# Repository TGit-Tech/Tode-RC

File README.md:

-----------------------------------------------------------------------------------
# Tode-RC
-----------------------------------------------------------------------------------
A User-Interfaced Arduino Mega Pro with Ebyte LoRa Radio.\
It's like a RF-Node but call it a 'Tode'.

- Arduino Mini Mega 2560 compatible Micro-Controller
- 1.8" TFT Display and 6-Button Keypad
- User friendly On-Controller IO configuration

See the docs/ Users-Guide for device support list and usage details including MQTT OpenHab connection abilities.

Benefits of the Tode over ESP32 LoRa Modules
- Big enough to be practical.  Small enough to be handy.
- 5V TTL-IO (Ebyte-RF 5V match, 200mW/IO power, Ready-fit for 5V Sensors)
- 54-IO pins (leaving (46) with display, keypad, radio connected)
- 30dbm (T30D) Transmission Power with Ebyte LoRa Modules (A good 5-mile distance)
- 3-Piece plug-together assembly keeps individual parts easy to swap/salvage.

Due to button sticking issues the buttons are now just black tops shown in first image.

-----------------------------------------------------------------------------------
#Project Purchase Options
-----------------------------------------------------------------------------------
Purchase pre-made at...
- https://www.tindie.com/stores/tgittech/
- https://www.etsy.com/shop/TGitTech

-----------------------------------------------------------------------------------
#Project Firmware & Expansions
-----------------------------------------------------------------------------------
- Firmware at https://github.com/TGit-Tech/Tode-RC-Firmware
	- Be sure to set Backplane model in config.h
- Side-IO Screw Terminals #SIOST (pictured) https://github.com/TGit-Tech/Tode-IO
- Back-IO Pin Header Array #BIOPH https://github.com/TGit-Tech/Tode-IO

-----------------------------------------------------------------------------------
#Project Status
-----------------------------------------------------------------------------------
USE Tode-RC.BD241S.  It supports 1W(T30D) or 1/4W(T20D) Ebyte Radios.\
Double Check that the PCB doesn't have the below design error.

Model SD23CF(In-Design/BETA) supports 2W(T33D) Radios but only 7-IO pins.
	
- Previous Release Notes
NEW changes.  The old model SA212K with analog keypad will become obsolete (not supported).
All future designs will have digital keypads as analog was spotty with moisture and 
temperature change.  Secondary Power Supplies are On-PCB now for both SD23CF(Side-IO) 
and BD241S(Back-IO).  Firmware will auto-detect E32-433T20D/T30D, E22-400T30D/900T30D 
and E220-400T30D Ebyte Radios.

---

# 🌐 **Tode Ecosystem**

The Tode Ecosystem offers a robust, flexible, and secure solution for managing devices in an environment where **infrastructure is not required**. It’s designed to seamlessly integrate with the **RF-DITS** protocol, providing a communication framework for device control, alarm propagation, and security.

## 🚀 **Overview**

The Tode Ecosystem empowers devices to function autonomously or in **P2P** (peer-to-peer) networks, providing an **infrastructure-free solution** for industrial, home, and remote applications. With its **5V EMT-resistant hardware** and powerful **virtual device** logic for alarm processing, it brings resilience and versatility to the edge of your network.

---

## 🛠️ **Key Features**

* **Non-Infrastructure Communication**: Operates **without** requiring an internet connection, server, or cloud dependencies. Devices communicate **peer-to-peer** between nodes, allowing for seamless data exchange and control.

* **RF-DITS Protocol**: The core communication protocol used by the Tode ecosystem. This protocol allows secure, fast, and efficient communication between Master and Remote nodes using **Device Index Tables (DIT)** with integrated security.

* **5V EMT Resistance**: Built to handle harsh environments, the Tode ecosystem is engineered to withstand **electromagnetic interference (EMI)**, providing reliable operation in industrial settings.

* **Virtual Device Logic**: The **Virtual Device Logic** allows users to implement custom control logic directly on the device, enabling real-time alarm processing, device manipulation, and other control functions.

* **Quick Firmware Updates**: The firmware can be quickly updated by plugging the Tode node into a wiring interface, making updates straightforward without requiring specialized equipment.

---

## 🔒 **Security**

* **SecNet (Security Network)**: The Tode ecosystem utilizes **SecNet**, a user-set security code embedded in each packet. This ensures data integrity and security. The **SecNet** code is also used as part of a challenge-response mechanism during **SETVAL** operations, preventing replay attacks and ensuring secure value updates.

* **Packet Integrity**: Every packet transmitted in the Tode network is verified for authenticity with the **SecNet** code. Only authorized devices can send or receive data securely. **SETVAL** operations are particularly secured to ensure legitimate communication.

* **Alarm Security**: Alarm messages are pushed to the designated **Remote nodes** when a condition is triggered. The **SecNet** code ensures that only authorized recipients receive the alarm notifications.

---

## ⚡ **Quick Setup & Control**

* **Device Setup**: The Tode ecosystem doesn’t require centralized infrastructure or cloud servers. Each **Master node** stores the configuration of its attached devices and is capable of sharing this configuration with **Remote nodes** using the **RF-DITS protocol**. **Remote nodes** can pull configurations and control devices according to those settings.

* **Time-Sensitive Updates**: Alarm conditions are pushed immediately to all **Remote nodes** without unnecessary overhead. Value updates can be requested by the remote node through the **RF-DITS protocol**, ensuring efficient communication.

---

## 📈 **Key Advantages Over Common IoT Platforms**

| **Key Advantage**             | **Tode Ecosystem (RF-DITS)**                                                                           | **Common IoT Platforms**                                                        |
| ----------------------------- | ------------------------------------------------------------------------------------------------------ | ------------------------------------------------------------------------------- |
| **Infrastructure**            | Operates **without** internet or server dependencies, functioning in **peer-to-peer** mode.            | Requires cloud, servers, or centralized hubs for device control                 |
| **Portability**               | **Portable** control with remote nodes in P2P communication.                                           | Typically dependent on fixed infrastructure                                     |
| **Data Integrity**            | Secured communication with **SecNet** protecting packets and ensuring valid data exchange.             | Often lacks robust security or packet verification                              |
| **Low Airtime Communication** | Optimized communication with **DIT** table, reducing airtime usage for value exchanges.                | Typically uses more airtime due to polling systems and continuous communication |
| **Alarm Handling**            | **One-time push** of alarms to Remote nodes, minimizing network traffic.                               | Continuous polling for alarm conditions, leading to higher network usage        |
| **Device Control**            | Full **control** over devices with direct value setting, updating, and logic processing.               | Remote devices may be read but not easily controlled depending on the platform  |
| **EMT Resistance**            | Designed to handle **electromagnetic interference (EMI)** in industrial environments.                  | Sensitive to environmental EMI interference, which can disrupt performance      |
| **Firmware Updates**          | **Easy and fast** firmware updates via a wiring interface—no internet or specialized equipment needed. | Over-the-air updates typically require internet access and cloud dependencies   |
| **Flexible Control Logic**    | **Virtual device logic** allows for custom control and alarm processing locally on the device.         | Often lacks flexibility for local control and relies on cloud logic             |

---

## ⚙️ **Protocol Breakdown: RF-DITS**

### **Device Index Table with Security (DITS)**

Each node maintains a **Device Index Table (DIT)** that lists the connected devices by index. This table helps the **Master node** store and transmit configurations for each attached device to **Remote nodes**.

* **Master Node**: Stores and manages the configuration of devices, pushes alarm notifications, and shares device settings with **Remote nodes**.
* **Remote Node**: Pulls device configurations from the **Master node** and can manipulate values according to the stored configuration.

### **Alarms**

* **Alarm Handling**: When an alarm condition is triggered on the **Master node**, an alarm packet is sent to all **Remote nodes** on the recipient list.
* **No Acknowledgment Required**: The alarm is a **one-time push** with no response required from the **Remote nodes**.
* **Alarm Recipient List**: The **Master node** stores a list of **Remote node** addresses, which is dynamically updated with each communication, including value requests. Manual pruning of the list is also possible.

---

## 🔗 **Integration with External Systems**

While the Tode ecosystem operates **without the need for internet infrastructure**, it can optionally integrate with systems such as **MQTT**, **OpenHAB**, or **Home Assistant** through an MQTT bridge.

This optional feature allows:

* **Pulling Device Values**: Remote nodes can request device values from **Master nodes** on a regular schedule or based on events.
* **Pushing Alarms**: When an alarm condition is triggered, the **Master node** can push the alarm data to an MQTT broker, which allows external systems to act on the alarm.

However, it's important to note that **Tode's core functionality** works without cloud connectivity, and the MQTT integration is entirely optional.

---

## 🔑 **Hardware Advantages**

Tode nodes are designed to operate in **industrial environments** where **electromagnetic interference (EMI)** is common, and devices need to withstand harsh conditions. The **5V EMT-resistant hardware** ensures the Tode ecosystem works reliably even in settings that may disrupt other IoT systems.

---

## 🛠️ **Getting Started**

1. **Set Up the Master Node**: Connect and configure devices on the **Master node**. Store configurations and define which devices you want to control.
2. **Add Remote Nodes**: Manually enter the **Master node's** address into the **Remote nodes** to establish communication and pull device configurations.
3. **Manage Alarms and Control**: Configure alarm conditions on the **Master node**. Alarms will be **pushed** to all **Remote nodes**.
4. **Firmware Updates**: Simply plug the Tode node into the wiring interface to update its firmware without requiring internet access.

---

## 📚 **Conclusion**

The **Tode Ecosystem** offers a resilient, flexible, and secure solution for edge-device control in environments where **infrastructure** is not an option. Its core **RF-DITS protocol** and **5V EMT resistance** provide reliable communication, while its optional integration with systems like **MQTT** makes it versatile for a range of applications.

---

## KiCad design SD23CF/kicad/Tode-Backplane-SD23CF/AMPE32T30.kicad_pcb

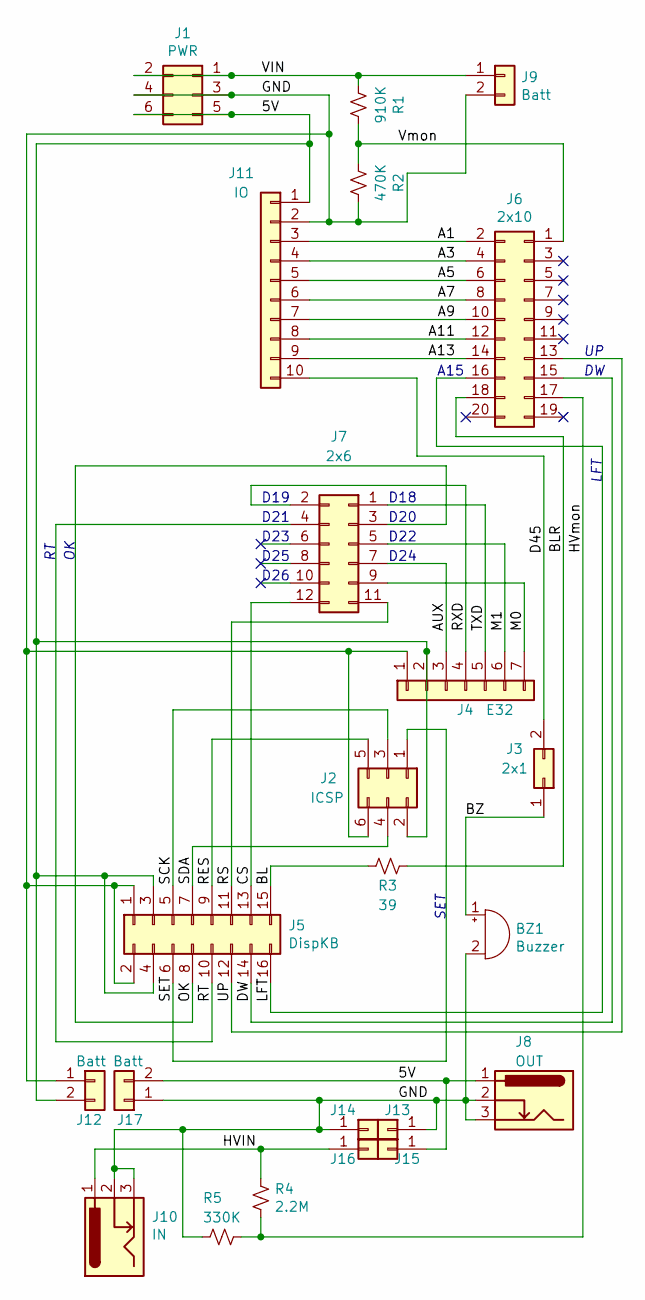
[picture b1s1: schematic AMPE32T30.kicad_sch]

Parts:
BZ1: Buzzer; MagneticBuzzer_PUI_AT-0927-TT-6-R
J1: PWR; PinSocket_2x03_P2.54mm_Vertical
J2: ICSP; PinHeader_2x03_P2.54mm_Vertical
J3: 2x1; PinSocket_1x02_P2.54mm_Vertical
J4: E32; PinSocket_1x07_P2.54mm_Vertical
J5: DispKB; PinSocket_2x08_P2.54mm_Vertical
J6: 2x10; PinSocket_2x10_P2.54mm_Vertical
J7: 2x6; PinSocket_2x06_P2.54mm_Vertical
J8: OUT; BarrelJack_Horizontal
J9, J12, J17: Batt; SolderWire-0.5sqmm_1x02_P4.6mm_D0.9mm_OD2.1mm
J10: IN; BarrelJack_Horizontal
J11: IO; PinSocket_1x10_P2.54mm_Vertical
J13: 13; PinSocket_1x01_P2.54mm_Vertical
J14: 14; PinSocket_1x01_P2.54mm_Vertical
J15: 15; PinSocket_1x01_P2.54mm_Vertical
J16: 16; PinSocket_1x01_P2.54mm_Vertical
R1: 910K; R_0805_2012Metric_Pad1.20x1.40mm_HandSolder
R2: 470K; R_0805_2012Metric_Pad1.20x1.40mm_HandSolder
R3: 39; R_0805_2012Metric_Pad1.20x1.40mm_HandSolder
R4: 2.2M; R_0805_2012Metric_Pad1.20x1.40mm_HandSolder
R5: 330K; R_0805_2012Metric_Pad1.20x1.40mm_HandSolder

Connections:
/5V: J1.5, J1.6, J2.2, J4.2, J5.3, J5.4, J8.1, J11.1, J12.2, J15.1, J17.2
/A1: J6.2, J11.3
/A3: J6.4, J11.4
/A5: J6.6, J11.5
/A7: J6.8, J11.6
/A9: J6.10, J11.7
/A11: J6.12, J11.8
/A13: J6.14, J11.9
/AUX: J4.3, J7.7
/BL: J5.15, R3.2
/BLR: J6.18, R3.1
/BZ: BZ1.1 (-), J3.1
/CS: J5.13, J7.12
/D45: J3.2, J11.10
/DW: J5.14, J6.15
/GND: BZ1.2 (+), J1.3, J1.4, J2.6, J4.1, J5.1, J5.2, J8.2, J8.3, J9.2, J10.2, J10.3, J11.2, J12.1, J13.1, J14.1, J17.1, R2.1, R5.2
/HVIN: J10.1, J16.1, R4.2
/HVmon: J6.17, R4.1, R5.1
/LFT: J5.16, J6.16
/M0: J4.7, J7.9
/M1: J4.6, J7.5
/OK: J5.8, J7.3
/RES: J2.5, J5.9
/RS: J5.11, J7.11
/RT: J5.10, J7.4
/RXD: J4.4, J7.2
/SCK: J2.3, J5.5
/SDA: J2.4, J5.7
/SET: J2.1, J5.6
/TXD: J4.5, J7.1
/UP: J5.12, J6.13
/VIN: J1.1, J1.2, J9.1, R1.2
/Vmon: J6.1, R1.1, R2.2

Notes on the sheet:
LFT
D18
D25
SET
D23
D24
D20
D26
D19
A15
D22
D21

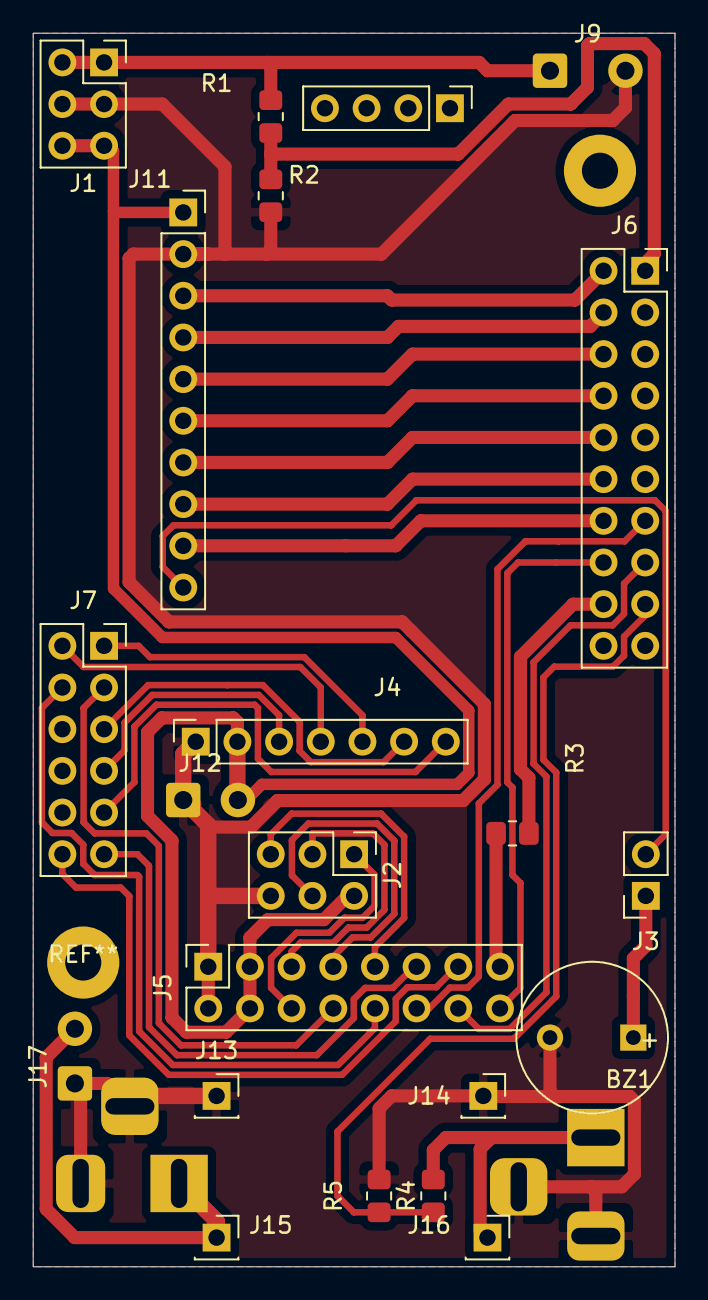
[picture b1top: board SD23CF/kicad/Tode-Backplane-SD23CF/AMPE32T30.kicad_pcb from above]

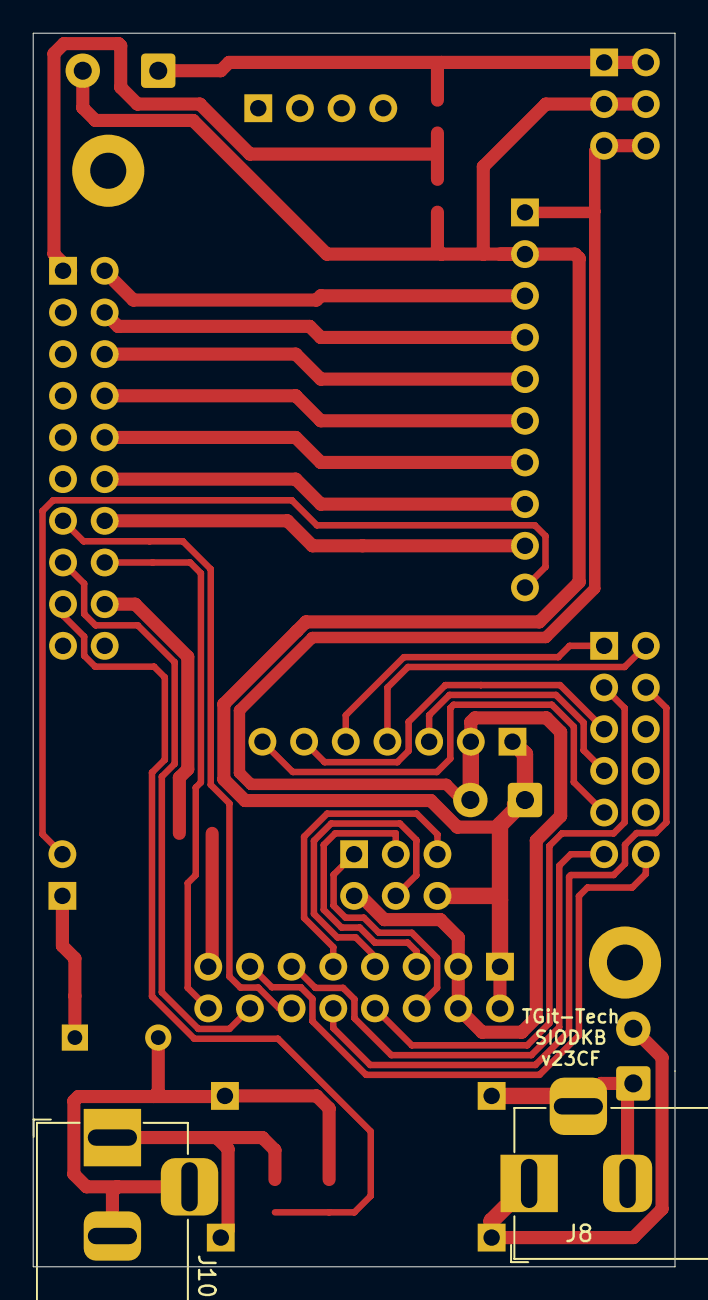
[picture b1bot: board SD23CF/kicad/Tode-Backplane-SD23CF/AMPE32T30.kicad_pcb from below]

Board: 2 copper layers, 39.1 x 75.2 mm, 23 parts (2 on the bottom side), 33 nets.

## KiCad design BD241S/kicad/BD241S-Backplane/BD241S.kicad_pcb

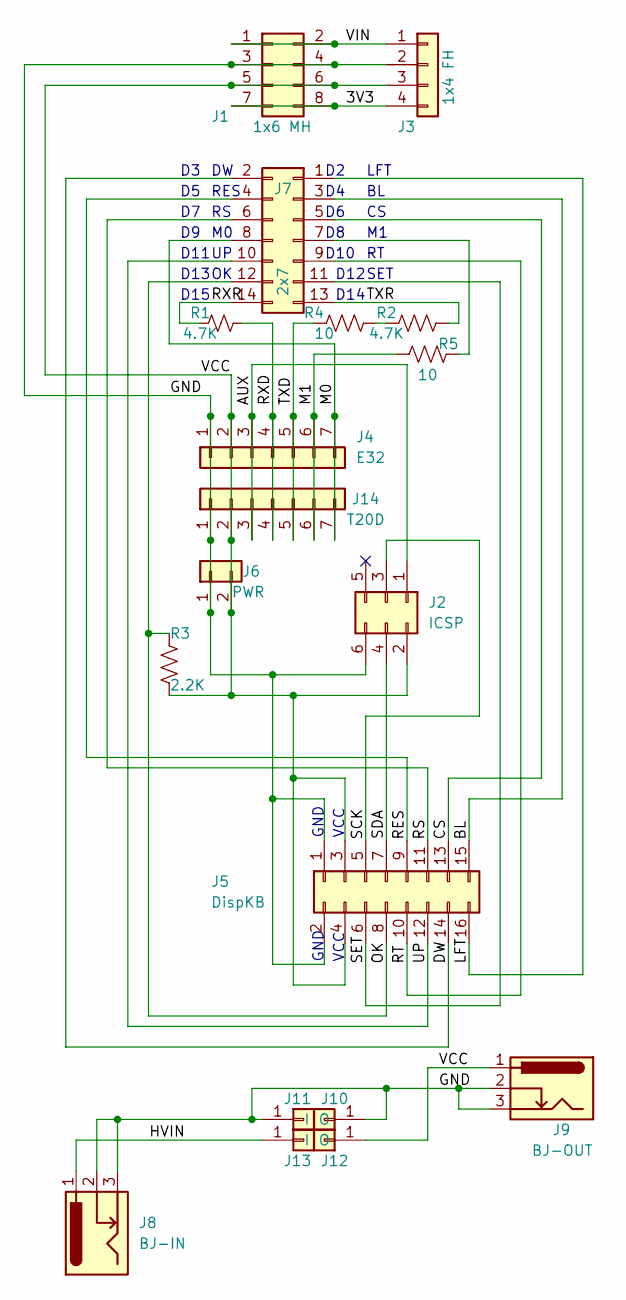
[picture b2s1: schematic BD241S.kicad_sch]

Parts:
J1: 1x6 MH; PinSocket_2x04_P2.54mm_Vertical
J2: ICSP; PinHeader_2x03_P2.54mm_Vertical
J3: 1x4 FH; PinSocket_1x04_P2.54mm_Vertical
J4: E32; PinSocket_1x07_P2.54mm_Vertical
J5: DispKB; PinSocket_2x08_P2.54mm_Vertical
J6: PWR; PinSocket_1x02_P2.54mm_Vertical
J7: 2x7; PinSocket_2x07_P2.54mm_Vertical
J8: BJ-IN; BarrelJack_Horizontal
J9: BJ-OUT; BarrelJack_Horizontal
J10, J12: O; PinSocket_1x01_P2.54mm_Vertical
J11, J13: I; PinSocket_1x01_P2.54mm_Vertical
J14: T20D; PinSocket_1x07_P2.54mm_Vertical
R1, R2: 4.7K; R_0805_2012Metric_Pad1.20x1.40mm_HandSolder
R3: 2.2K; R_0805_2012Metric_Pad1.20x1.40mm_HandSolder
R4, R5: 10; R_0805_2012Metric_Pad1.20x1.40mm_HandSolder

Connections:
/3V3: J1.7, J1.8, J3.4
/AUX: J2.1, J4.3, J14.3
/BL: J5.15, J7.3
/CS: J5.13, J7.5
/DW: J5.14, J7.2
/GND: J1.3, J1.4, J2.6, J3.2, J4.1, J5.1, J5.2, J6.1, J8.2, J8.3, J9.2, J9.3, J10.1, J11.1, J14.1
/HVIN: J8.1, J13.1
/LFT: J5.16, J7.1
/M0: J4.7, J7.8, J14.7
/M1: J4.6, J14.6, R5.1
/OK: J5.8, J7.12, R3.2
/RES: J5.9, J7.4
/RS: J5.11, J7.6
/RT: J5.10, J7.9
/RXD: J4.4, J14.4, R1.1
/RXR: J7.14, R1.2
/SCK: J2.3, J5.5
/SDA: J2.4, J5.7
/SET: J5.6, J7.11
/TXD: J4.5, J14.5, R4.1
/TXR: J7.13, R2.2
/UP: J5.12, J7.10
/VCC: J1.5, J1.6, J2.2, J3.3, J4.2, J5.3, J5.4, J6.2, J9.1, J12.1, J14.2, R3.1
/VIN: J1.1, J1.2, J3.1
unnamed: J7.7, R5.2
unnamed: R2.1, R4.2

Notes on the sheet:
GND
LFT
D13
RES
SET
D12
D15
VCC
D14
D10
D11

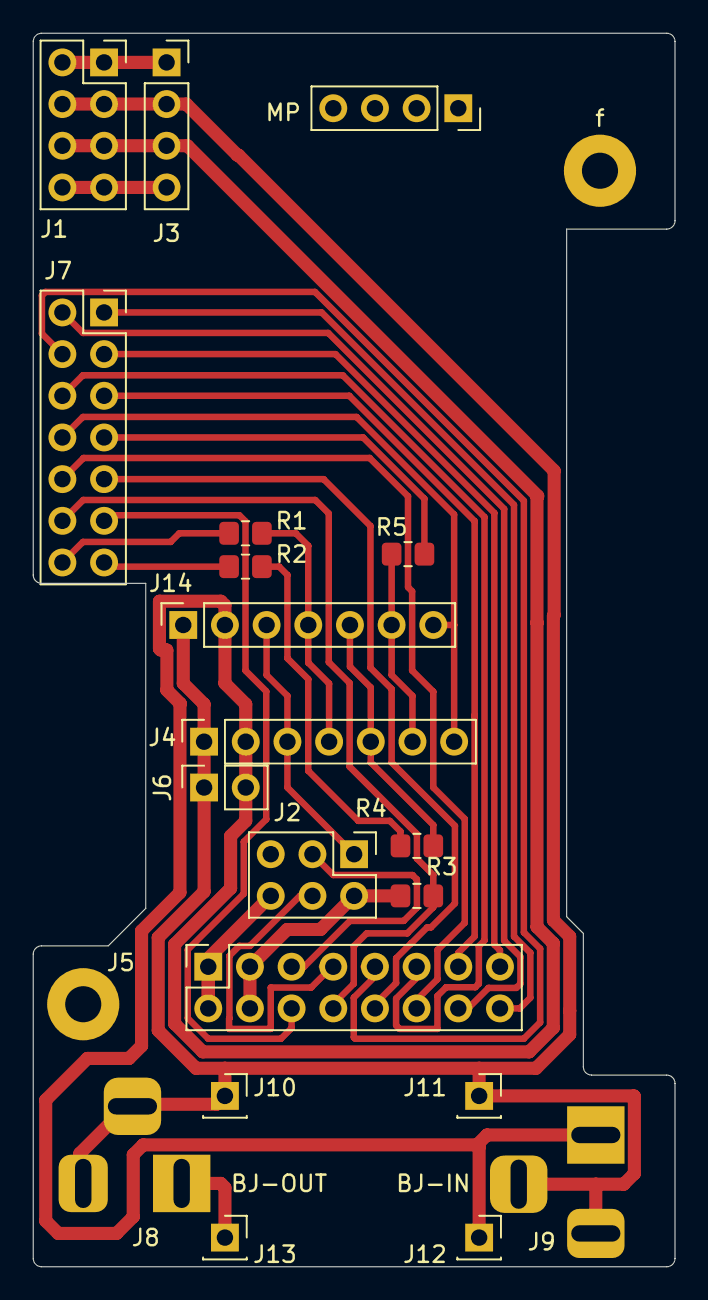
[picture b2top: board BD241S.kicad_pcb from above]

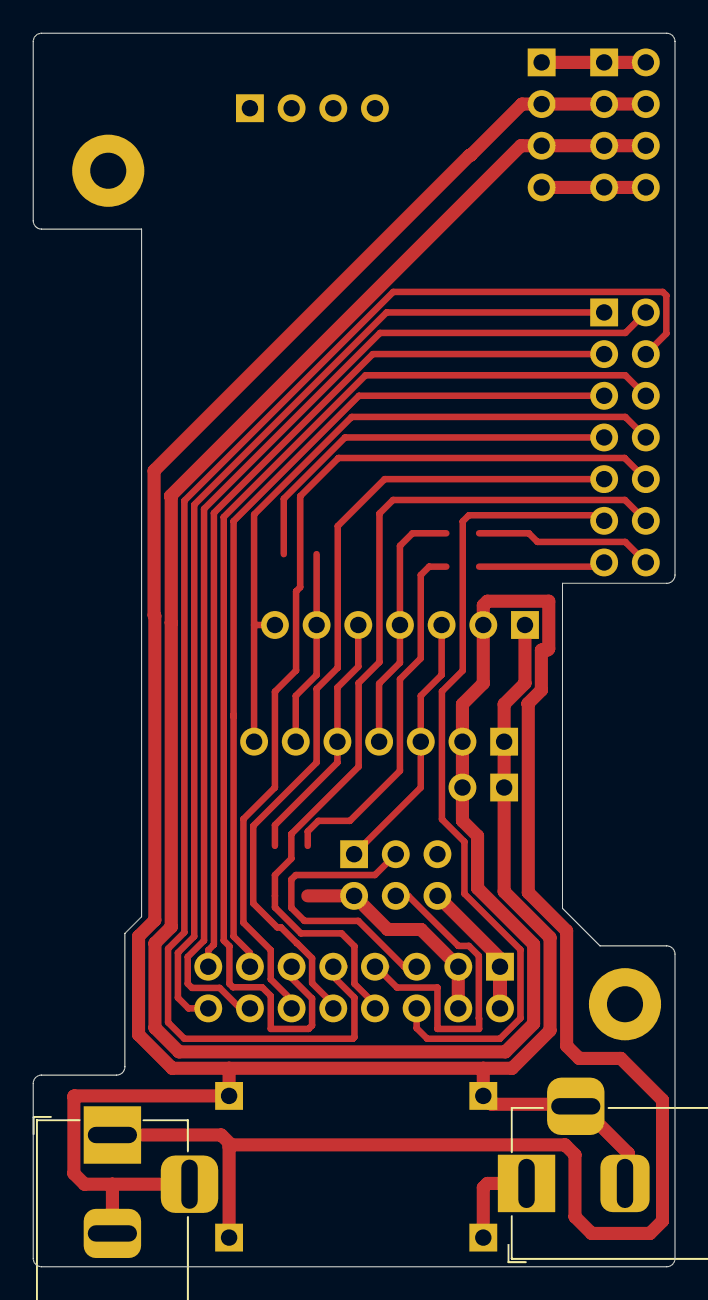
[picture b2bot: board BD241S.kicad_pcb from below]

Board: 2 copper layers, 39.1 x 75.2 mm, 22 parts (2 on the bottom side), 26 nets.

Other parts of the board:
MP: PinSocket_1x04_P2.54mm_Vertical
e: MountingHole_2.2mm_M2_Pad
f: MountingHole_2.2mm_M2_Pad

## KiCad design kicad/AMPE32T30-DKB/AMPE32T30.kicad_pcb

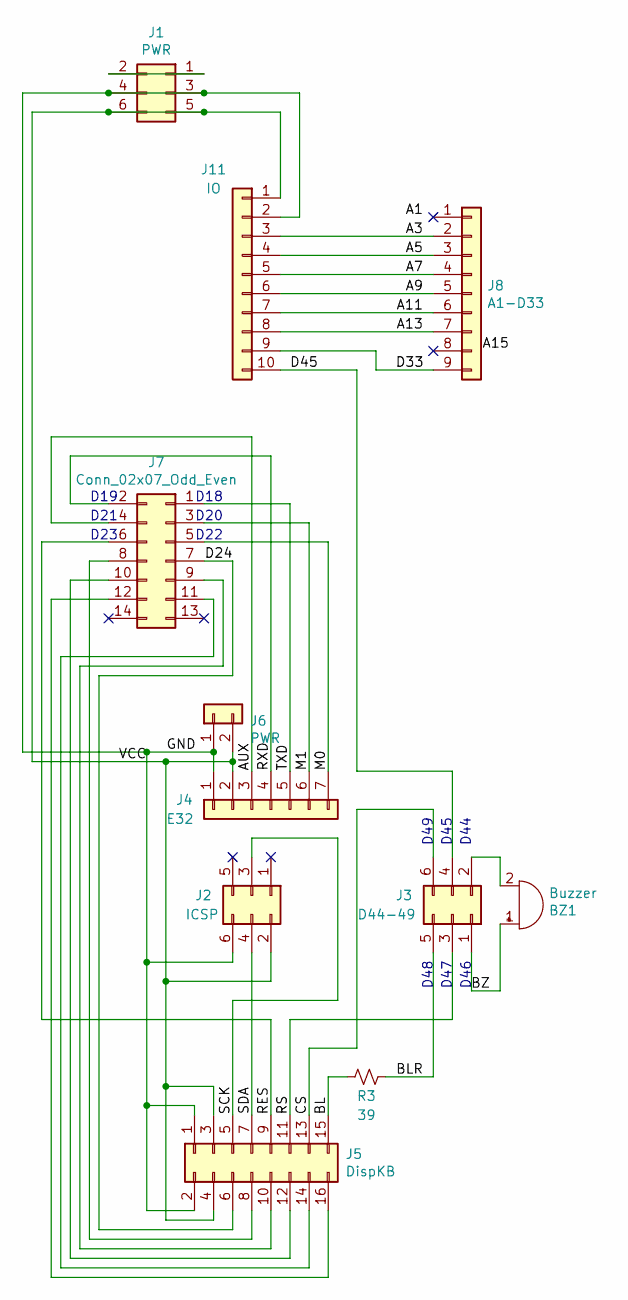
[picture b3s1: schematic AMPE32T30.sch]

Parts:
BZ1: Buzzer; MagneticBuzzer_PUI_AT-0927-TT-6-R
J1: PWR; PinSocket_2x03_P2.54mm_Vertical
J2: ICSP; PinHeader_2x03_P2.54mm_Vertical
J3: D44-49; PinSocket_2x03_P2.54mm_Vertical
J4: E32; PinSocket_1x07_P2.54mm_Vertical
J5: DispKB; PinSocket_2x08_P2.54mm_Vertical
J6: PWR; PinSocket_1x02_P2.54mm_Vertical
J7: Conn_02x07_Odd_Even; PinSocket_2x07_P2.54mm_Vertical
J8: A1-D33; PinSocket_1x09_P2.54mm_Vertical
J11: IO; PinSocket_1x10_P2.54mm_Vertical
R3: 39; R_0805_2012Metric_Pad1.20x1.40mm_HandSolder

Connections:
/A3: J8.2, J11.3
/A5: J8.3, J11.4
/A7: J8.4, J11.5
/A9: J8.5, J11.6
/A11: J8.6, J11.7
/A13: J8.7, J11.8
/AUX: J4.3, J7.4
/BL: J5.15, R3.2
/BLR: J3.5, R3.1
/BZ: BZ1.1 (-), J3.1
/CS: J3.6, J5.13
/D24: J5.6, J7.7
/D33: J8.9, J11.9
/D45: J3.4, J11.10
/GND: J1.3, J1.4, J2.6, J4.1, J5.1, J5.2, J6.1, J11.2
/M0: J4.7, J7.5
/M1: J4.6, J7.3
/RES: J5.9, J7.6
/RS: J3.3, J5.11
/RXD: J4.4, J7.2
/SCK: J2.3, J5.5
/SDA: J2.4, J5.7
/TXD: J4.5, J7.1
/VCC: J1.5, J1.6, J2.2, J4.2, J5.3, J5.4, J6.2, J11.1
unnamed: BZ1.2 (+), J3.2
unnamed: J1.1, J1.2
unnamed: J5.8, J7.8
unnamed: J5.10, J7.9
unnamed: J5.12, J7.10
unnamed: J5.14, J7.11
unnamed: J5.16, J7.12

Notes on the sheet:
D46
D47
D48
D49
D45
D44
D23
D21
D19
D18
D20
D22

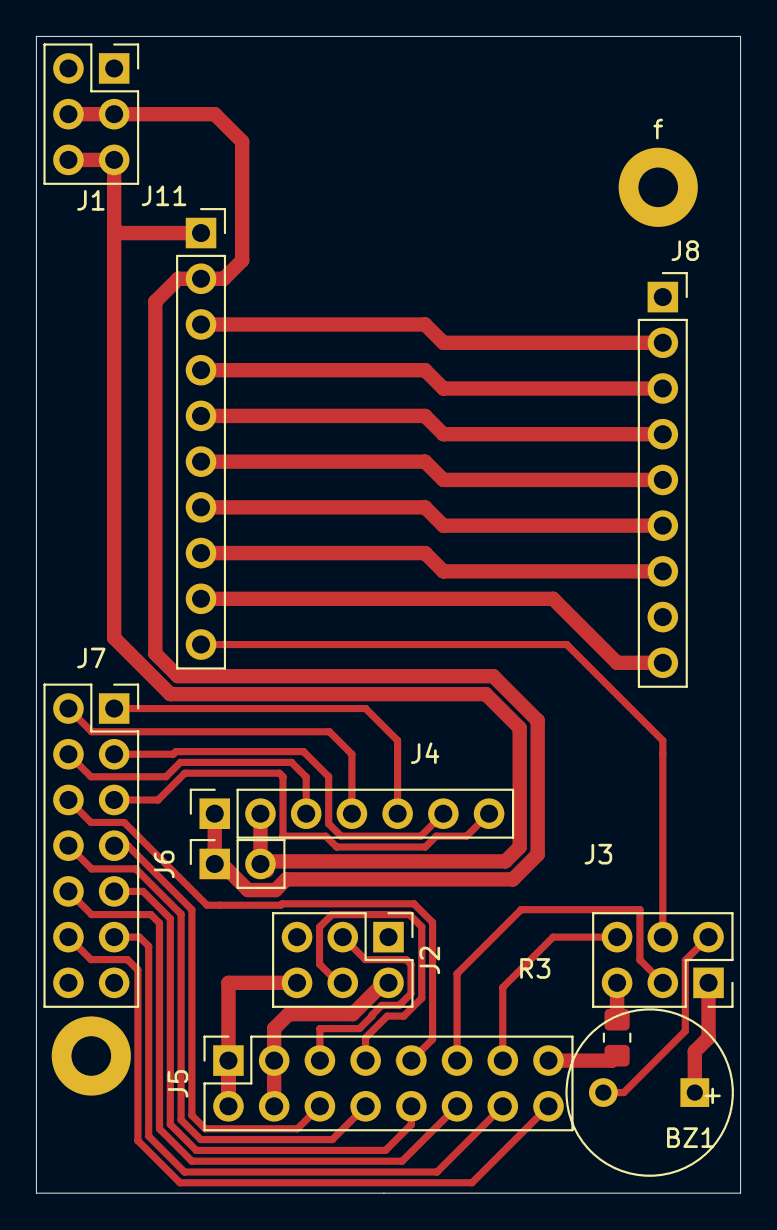
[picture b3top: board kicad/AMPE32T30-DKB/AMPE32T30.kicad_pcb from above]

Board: 2 copper layers, 39.1 x 64.3 mm, 13 parts (0 on the bottom side), 31 nets.

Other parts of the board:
e: MountingHole_2.2mm_M2_Pad
f: MountingHole_2.2mm_M2_Pad

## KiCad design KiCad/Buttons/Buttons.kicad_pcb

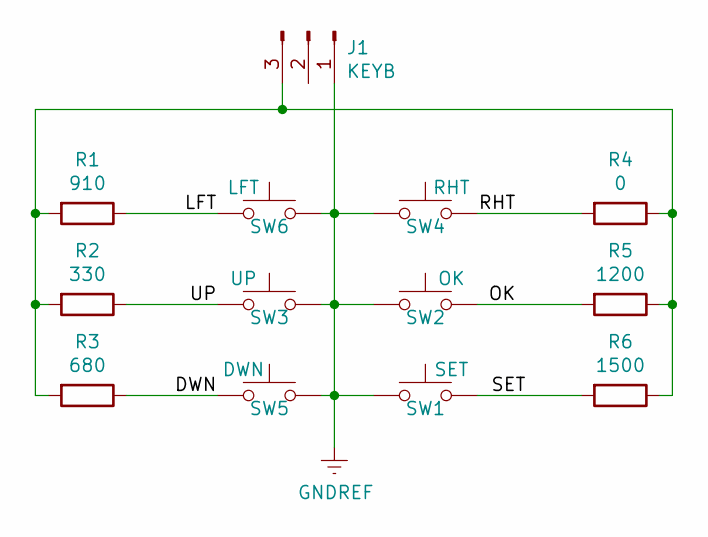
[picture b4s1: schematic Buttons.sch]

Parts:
J1: KEYB; PinHeader_1x03_P2.54mm_Vertical
R1: 910; R_0805_2012Metric
R2: 330; R_0805_2012Metric
R3: 680; R_0805_2012Metric
R4: 0; R_0805_2012Metric
R5: 1200; R_0805_2012Metric
R6: 1500; R_0805_2012Metric
SW1: SET; SW_PUSH_6mm
SW2: OK; SW_PUSH_6mm
SW3: UP; SW_PUSH_6mm
SW4: RHT; SW_PUSH_6mm
SW5: DWN; SW_PUSH_6mm
SW6: LFT; SW_PUSH_6mm

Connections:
/5V: J1.2; also elsewhere on the board
/AKB: J1.3, R1.2, R2.2, R3.2, R4.1, R5.1, R6.1
/DWN: R3.1, SW5.1
/LFT: R1.1, SW6.1
/OK: R5.2, SW2.2
/RHT: R4.2, SW4.2
/SET: R6.2, SW1.2
/UP: R2.1, SW3.1
GNDREF: J1.1, SW1.1, SW2.1, SW3.2, SW4.1, SW5.2, SW6.2; also elsewhere on the board

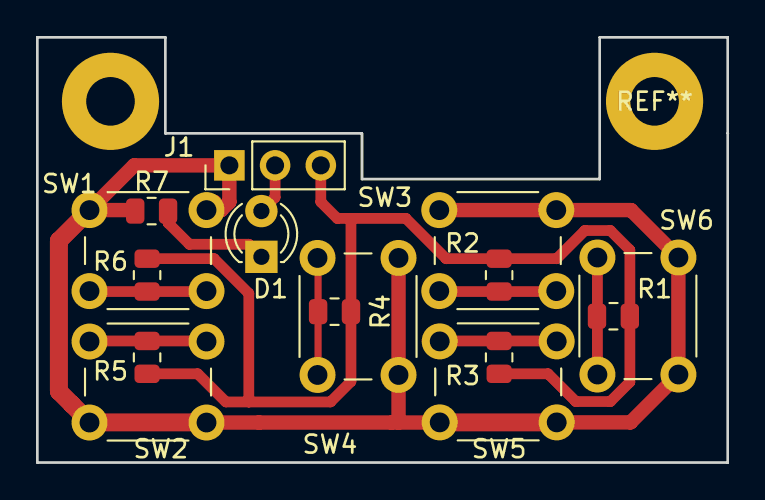
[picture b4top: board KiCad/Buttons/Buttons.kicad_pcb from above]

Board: 2 copper layers, 38.4 x 23.6 mm, 15 parts (0 on the bottom side), 10 nets.

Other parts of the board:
D1: LED; LED_D3.0mm
R7: R; R_0805_2012Metric

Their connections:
/5V: D1.2; also elsewhere on the board
GNDREF: R7.1; also elsewhere on the board
unnamed: D1.1, R7.2

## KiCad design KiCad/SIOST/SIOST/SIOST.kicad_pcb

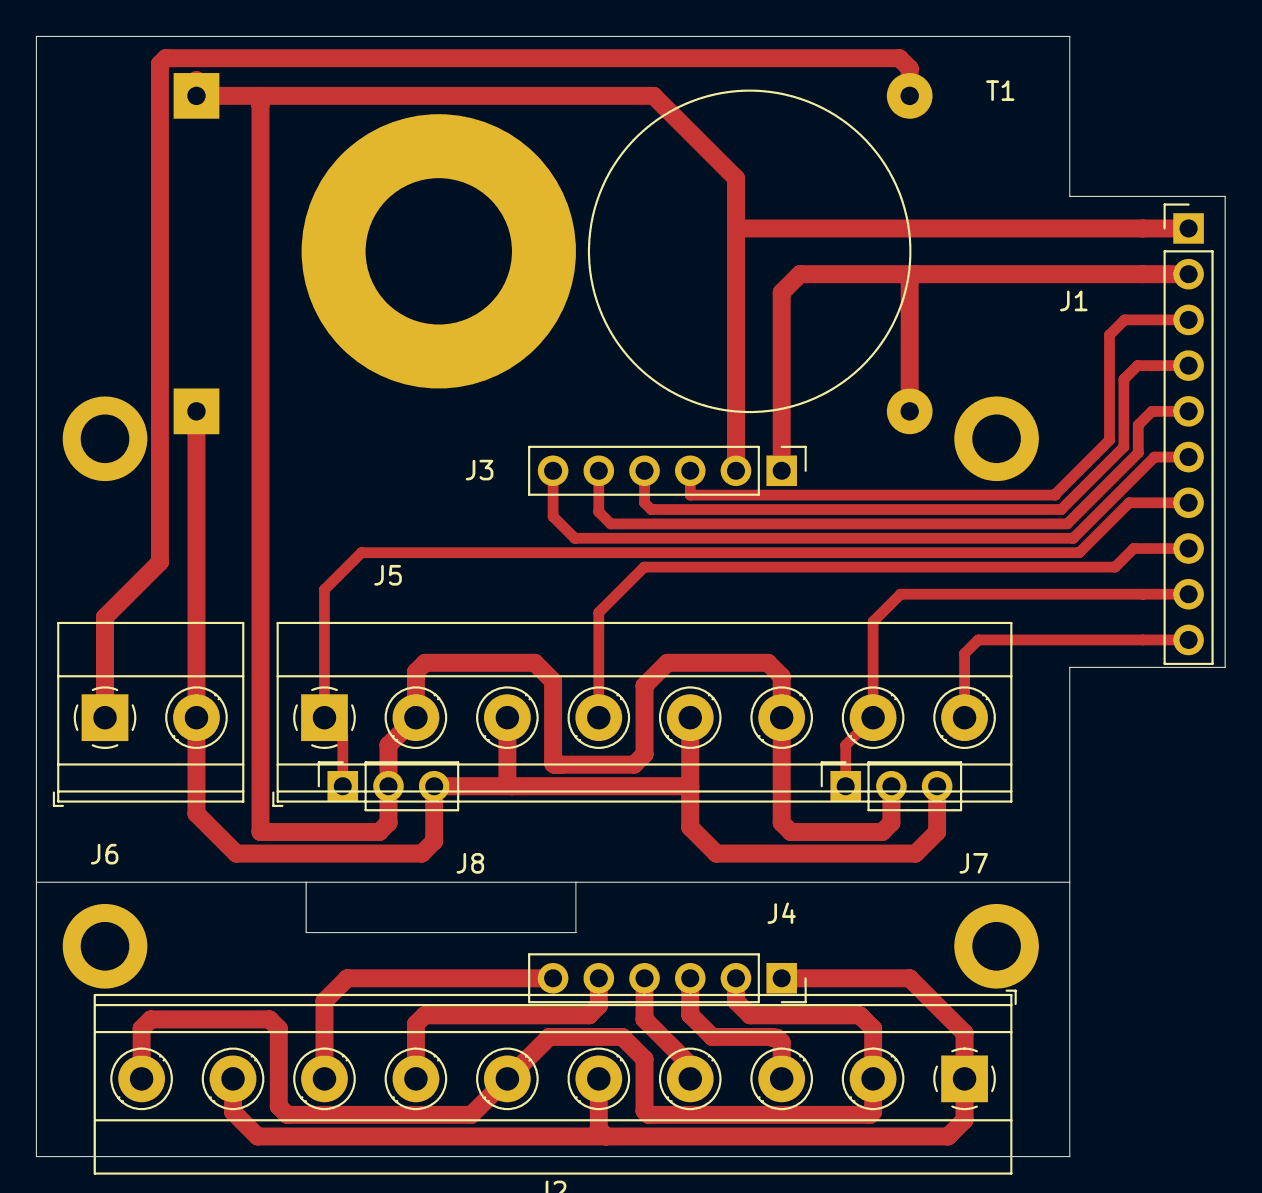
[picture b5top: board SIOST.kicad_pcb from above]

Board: 2 copper layers, 66.0 x 62.2 mm, 9 parts (0 on the bottom side), 17 nets.

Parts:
J1: IOP; PinHeader_1x10_P2.54mm_Vertical
J2: IOT; TerminalBlock_Phoenix_MKDS-1,5-10-5.08_1x10_P5.08mm_Horizon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
J3: IOM; PinHeader_1x06_P2.54mm_Vertical
J4: IOF; PinSocket_1x06_P2.54mm_Vertical
J5: IOB; TerminalBlock_Phoenix_MKDS-1,5-8-5.08_1x08_P5.08mm_Horizont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
J6: PWR; TerminalBlock_Phoenix_MKDS-1,5-2-5.08_1x02_P5.08mm_Horizont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
J7: RY1; PinSocket_1x03_P2.54mm_Vertical
J8: RY2; PinSocket_1x03_P2.54mm_Vertical
T1: LM2596; Transformer_Toroid_Horizontal_D18.0mm

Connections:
/3: J2.3, J4.3
/5: J2.4, J4.4
/5V: J1.1, J3.2, J5.2, J5.6, J7.2, J8.2, T1.4
/7: J2.7, J4.5
/9: J2.8, J4.6
/A3: J1.3, J3.3
/A5: J1.4, J3.4
/A7: J1.5, J3.5
/A9: J1.6, J3.6
/A11: J1.7, J5.1, J8.1
/A13: J1.8, J5.4
/D33: J1.9, J5.7, J7.1
/D45: J1.10, J5.8
/GND: J1.2, J3.1, J5.3, J5.5, J6.2, J7.3, J8.3, T1.1, T1.3
/VIN: J6.1, T1.2
unnamed: J2.1, J2.5, J2.9, J4.1
unnamed: J2.2, J2.6, J2.10, J4.2

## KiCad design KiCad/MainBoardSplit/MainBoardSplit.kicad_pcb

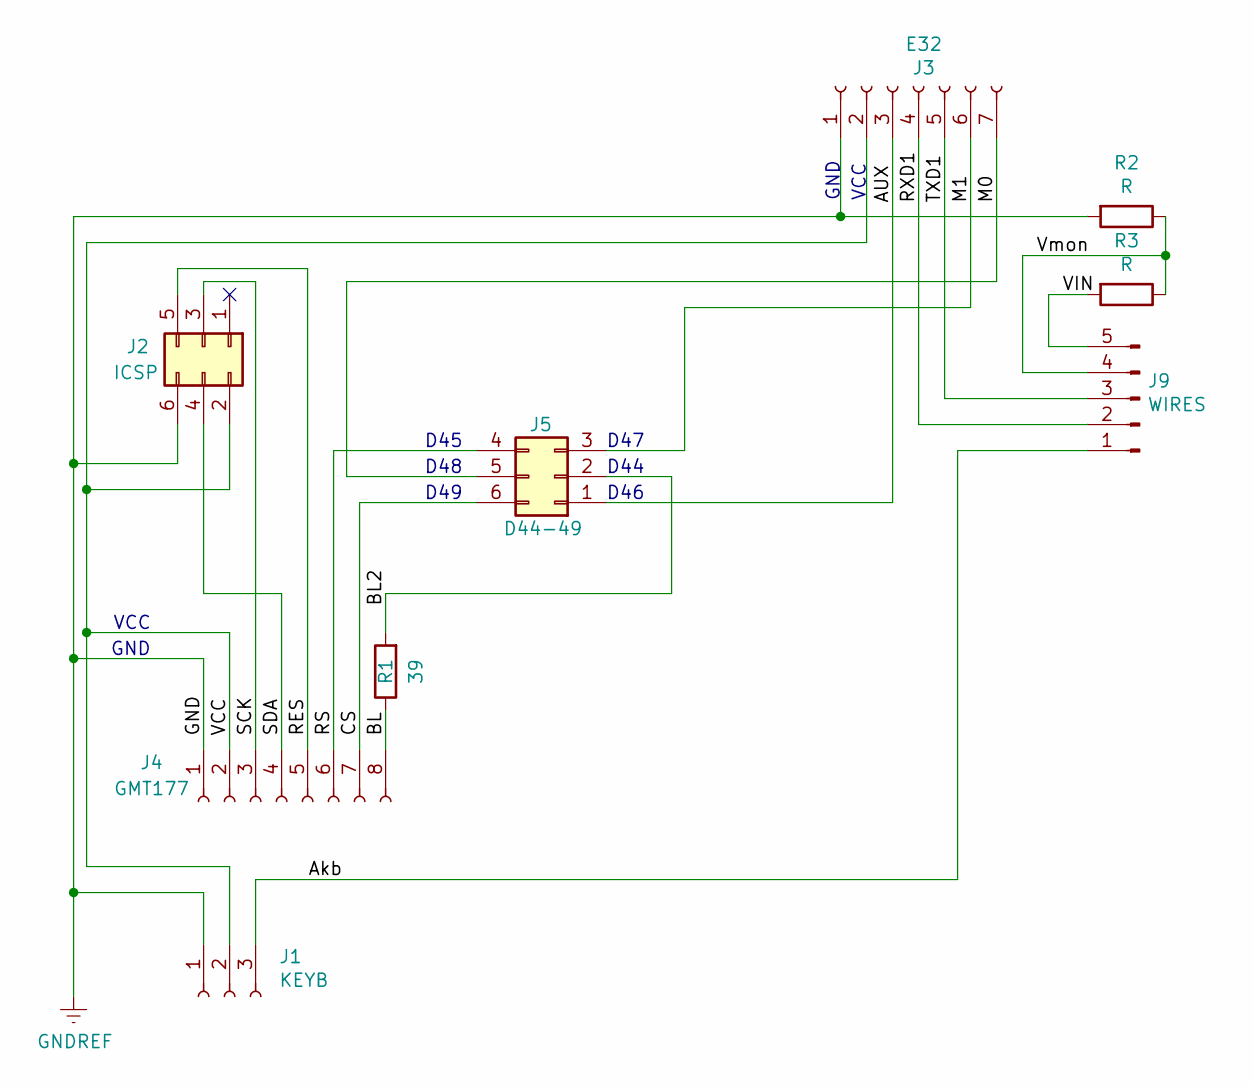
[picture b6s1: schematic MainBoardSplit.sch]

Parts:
J1: KEYB; PinSocket_1x03_P2.54mm_Vertical
J2: ICSP; PinHeader_2x03_P2.54mm_Vertical
J3: E32; PinSocket_1x07_P2.54mm_Vertical
J4: GMT177; PinSocket_1x08_P2.54mm_Vertical
J5: D44-49; PinHeader_2x03_P2.54mm_Vertical
J9: WIRES; PinHeader_1x05_P2.54mm_Vertical
R1: 39; R_0805_2012Metric_Pad1.15x1.40mm_HandSolder
R2, R3: R; R_0805_2012Metric

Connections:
/AUX: J3.3, J5.1
/Akb: J1.3, J9.1
/BL: J4.8, R1.1
/BL2: J5.2, R1.2
/CS: J4.7, J5.6
/M0: J3.7, J5.5
/M1: J3.6, J5.3
/RES: J2.5, J4.5
/RS: J4.6, J5.4
/RXD1: J3.4, J9.2
/SCK: J2.3, J4.3
/SDA: J2.4, J4.4
/TXD1: J3.5, J9.3
/VCC: J1.2, J2.2, J3.2, J4.2
/VIN: J9.5, R3.2
/Vmon: J9.4, R2.1, R3.1
GNDREF: J1.1, J2.6, J3.1, J4.1, R2.2

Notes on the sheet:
D46
D44
D47
D45
D48
D49
VCC
GND

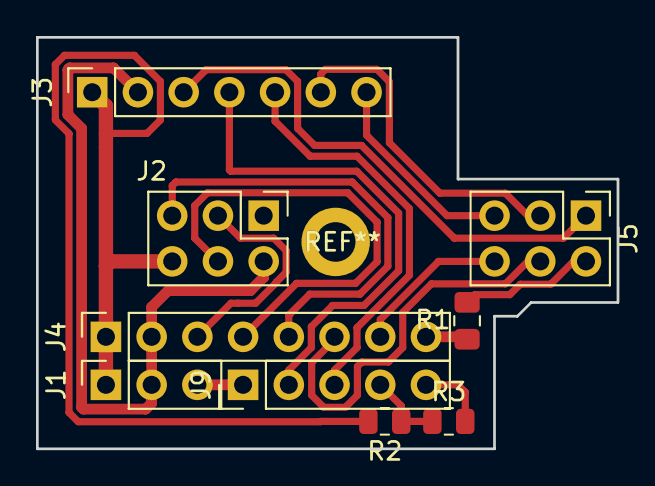
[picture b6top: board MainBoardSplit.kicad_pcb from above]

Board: 2 copper layers, 32.3 x 22.9 mm, 9 parts (0 on the bottom side), 17 nets.

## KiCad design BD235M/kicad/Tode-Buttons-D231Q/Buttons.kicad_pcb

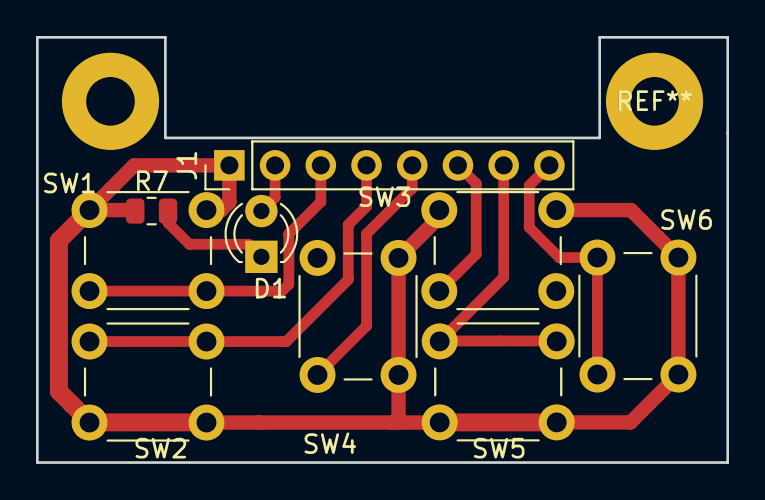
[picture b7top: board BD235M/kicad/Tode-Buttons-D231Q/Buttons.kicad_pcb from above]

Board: 2 copper layers, 38.4 x 23.6 mm, 9 parts (0 on the bottom side), 9 nets.

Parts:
D1: LED; LED_D3.0mm
J1: Conn_01x08_Male; PinHeader_1x08_P2.54mm_Vertical
R7: R; R_0805_2012Metric
SW1: SET; SW_PUSH_6mm
SW2: OK; SW_PUSH_6mm
SW3: UP; SW_PUSH_6mm
SW4: RHT; SW_PUSH_6mm
SW5: DWN; SW_PUSH_6mm
SW6: LFT; SW_PUSH_6mm

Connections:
/5V: D1.2, J1.2
/DWN: J1.7, SW5.1
/LFT: J1.8, SW6.1
/OK: J1.4, SW2.2
/RHT: J1.5, SW4.2
/SET: J1.3, SW1.2
/UP: J1.6, SW3.1
GNDREF: J1.1, R7.1, SW1.1, SW2.1, SW3.2, SW4.1, SW5.2, SW6.2
unnamed: D1.1, R7.2

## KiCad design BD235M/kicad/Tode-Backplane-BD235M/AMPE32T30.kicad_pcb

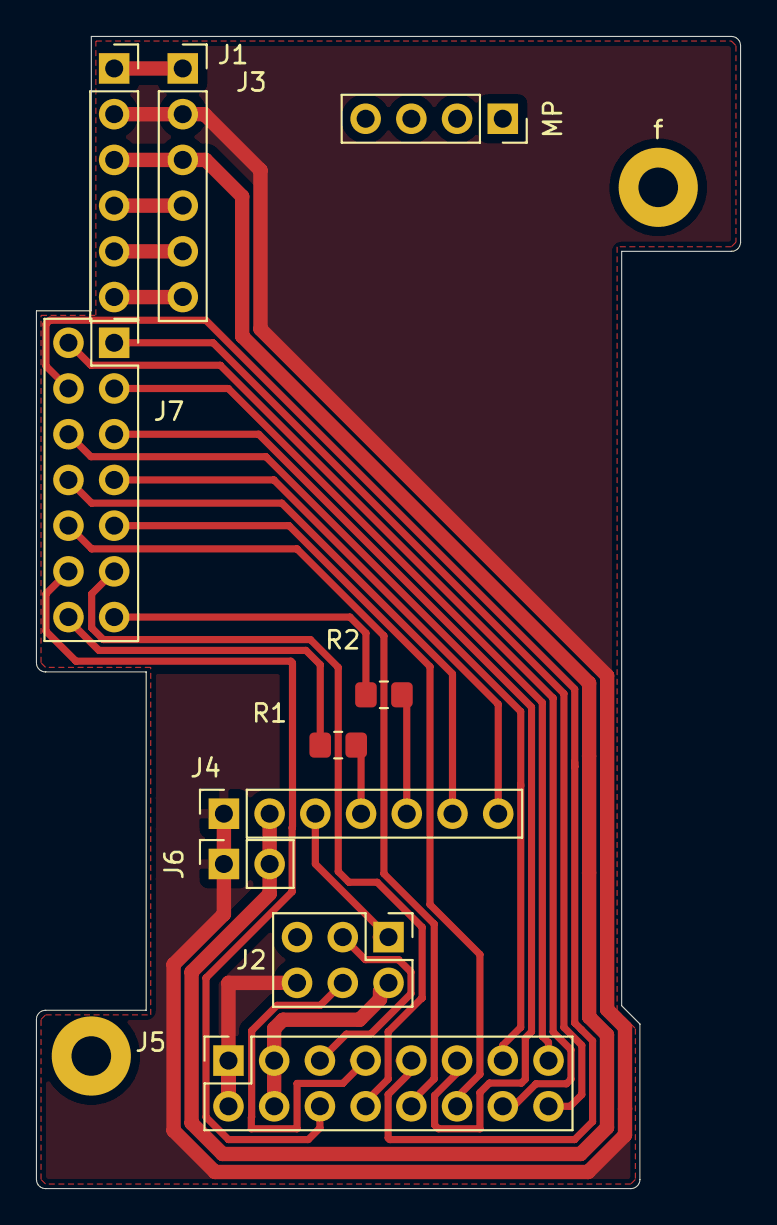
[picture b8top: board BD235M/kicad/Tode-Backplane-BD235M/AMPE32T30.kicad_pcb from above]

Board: 2 copper layers, 39.1 x 64.0 mm, 12 parts (0 on the bottom side), 25 nets.

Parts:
J1, J3: Conn_01x06; PinSocket_1x06_P2.54mm_Vertical
J2: ICSP; PinHeader_2x03_P2.54mm_Vertical
J4: E32; PinSocket_1x07_P2.54mm_Vertical
J5: DispKB; PinSocket_2x08_P2.54mm_Vertical
J6: PWR; PinSocket_1x02_P2.54mm_Vertical
J7: Conn_02x07_Odd_Even; PinSocket_2x07_P2.54mm_Vertical
MP: PinSocket_1x04_P2.54mm_Vertical
R1, R2: 39; R_0805_2012Metric_Pad1.20x1.40mm_HandSolder
e: MountingHole_2.2mm_M2_Pad
f: MountingHole_2.2mm_M2_Pad

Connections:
/3V3: J1.4, J3.4
/AREF: J1.5, J3.5
/AUX: J2.1, J4.3
/BL: J5.15, J7.3
/CS: J5.13, J7.6
/DW: J5.14, J7.2
/GND: J1.2, J2.6, J3.2, J4.1, J5.1, J5.2, J6.1
/LT: J5.16, J7.1
/M0: J4.7, J7.7
/M1: J4.6, J7.8
/OK: J5.8, J7.11
/RES: J5.9, J7.4
/RS: J5.11, J7.5
/RT: J5.10, J7.10
/RX: J1.6, J3.6
/RXD: J4.4, R1.1
/RXR: J7.14, R1.2
/SCK: J2.3, J5.5
/SDA: J2.4, J5.7
/SET: J5.6, J7.12
/TXD: J4.5, R2.1
/TXR: J7.13, R2.2
/UP: J5.12, J7.9
/VCC: J1.3, J2.2, J3.3, J4.2, J5.3, J5.4, J6.2
/VIN: J1.1, J3.1

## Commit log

2020-11-02 Initial
    Initial Plans
2020-11-27 Update
    Update
2020-12-12 Updates
    Updates
2021-01-20 Buggy Firmware Update
2021-01-21 211K update
2021-06-13 ver 2156
    Many Updates
2021-11-07 Update README.md
    update
2021-11-09 Final Doc
    Final Doc
2021-11-16 Doc Update
    Doc Update
2021-11-17 Update README.md
    purchase option builders
2021-11-18 21BH Firmware
    21BH firmware update
2021-11-19 Update iHdw.cpp
    Reset skips RFAddr and SecNet
2021-11-20 Create Tode-RC Manual - Users Guide.pdf
    Added user manual
2021-12-05 CriCut Display Stickers
    Updated Disp Stickers
2021-12-08 Moved Firmware to Tode-RC-Firmware
    Updated Readme
2021-12-08 Update README.md
    end of line
2021-12-08 Update README.md
    more readme fixes
2021-12-09 Doc Updates
2022-01-02 Button alignment Adjustments
    Model adjustments (minor). Reverse Compatible.
2022-01-26 CNC cut files in marked folder
2022-02-06 221N
2023-01-26 Added Digital KB (DKB)
    Updated User Manual added Digital KB DKB
2023-02-22 Update Tode-RC Manual - Users Guide.pdf
    Added MQTT support details
2023-02-28 getting gibhub manual io online
2023-02-28 online manual
2024-01-23 Multi Model
2024-02-21 SD23CF and BD241S
    Obsolete SA212K
2024-12-30 Cleaned up scrap work
    Cleaned up scrap work
2024-12-30 Removed
2025-01-10 Readme updates
    Readme updates
